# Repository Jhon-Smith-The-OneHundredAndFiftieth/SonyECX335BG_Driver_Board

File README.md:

# This is a driver board for the sony ECX335BG compatible with rasperi py (using the DPI interface)
Basicly a clone of https://github.com/aedancullen/sony-ecx with some things rewired

License : GPL-3.0
gnu.org/licenses/gpl-3.0

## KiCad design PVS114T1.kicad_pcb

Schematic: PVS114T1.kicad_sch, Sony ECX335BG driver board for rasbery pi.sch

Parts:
C1, C17, C22: 4.7uF; C0402
C2, C3, C4, C5, C6, C7, C8, C9, C10, C11, C12, C13, C14, C15, C19, C21: 0.1uF; C0402
C16: 1uF; C0402
C18, C20: 0.01uF; C0402
C23: 0.47uF; C0402
C24: 2.2uF; C0402
C25, C26: 10uF; C0402
J1: 61FVXS-RSM1-GAN-TF_LF__SN_; 61FVXSRSM1GANTFLFSN
J2: Conn_01x08_Male; PinHeader_1x08_P1.00mm_Vertical
JP1: PINHD-2X20; 2X20
L1: ME3220-682MLB; INDPM3228X240N
R1, R2: R0402
R3: 10K; R0402
RN1: YC248-JR-0710KL; YC248JR0710KL
U1: BU90T82-ZE2
U2: LT3473; SON50P300X300X80-9T165X238N
VR1: NCP1117ST33T3G; SOT230P700X170-4

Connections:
/D_6B8B: J2.3, U1.F7 (6B8B)
/D_B10: JP1.7, U1.H5 (B10)
/D_B11: JP1.29, U1.J5 (B11)
/D_B12: JP1.31, U1.H6 (B12)
/D_B13: JP1.26, U1.J6 (B13)
/D_B14: JP1.24, U1.H7 (B14)
/D_B15: JP1.21, U1.J7 (B15)
/D_B16: JP1.19, U1.H8 (B16)
/D_B17: JP1.23, U1.J8 (B17)
/D_CLKIN: JP1.27, U1.F9 (CLKIN)
/D_DDRN: J2.5, U1.E9 (DDRN)
/D_DE: JP1.28, U1.G9 (DE)
/D_FLIP: J2.1, U1.C2 (FLIP)
/D_G10: JP1.32, U1.H1 (G10)
/D_G11: JP1.33, U1.J1 (G11)
/D_G12: JP1.8, U1.H2 (G12)
/D_G13: JP1.10, U1.J2 (G13)
/D_G14: JP1.36, U1.H3 (G14)
/D_G15: JP1.11, U1.J3 (G15)
/D_G16: JP1.12, U1.H4 (G16)
/D_G17: JP1.35, U1.J4 (G17)
/D_HSYNC: JP1.5, U1.J9 (HSYNC)
/D_MAP: J2.2, U1.E8 (MAP)
/D_MODE: J2.4, U1.E7 (MODE)
/D_OE: J2.6, U1.D9 (OE)
/D_PWDN: R3.2, U1.D8 (PWDN)
/D_R10: JP1.38, U1.D2 (R10)
/D_R11: JP1.40, U1.D1 (R11)
/D_R12: JP1.15, U1.E2 (R12)
/D_R13: JP1.16, U1.E1 (R13)
/D_R14: JP1.18, U1.F2 (R14)
/D_R15: JP1.22, U1.F1 (R15)
/D_R16: JP1.37, U1.G2 (R16)
/D_R17: U1.G1 (R17)
/D_RF: J2.8, U1.G8 (RF)
/D_RS: J2.7, U1.F8 (RS)
/D_SI: RN1.4
/D_SI1V8: J1.52, RN1.1, RN1.3
/D_SO1V8: J1.51
/D_TEST: U1.C3 (TEST)
/D_VSYNC: JP1.3, U1.H9 (VSYNC)
/D_XCLR: RN1.12
/D_XCLR1V8: C4.2, J1.47, RN1.9, RN1.11
/D_XCS: RN1.8
/D_XCS1V8: J1.54, RN1.5, RN1.7
/D_XSCK: RN1.16
/D_XSCK1V8: J1.53, RN1.13, RN1.15
/N$1: C1.1, C17.1, J1.2, J1.60
/N$2: L1.1, U2.8 (SW)
/N$4: C23.1, R2.2, U2.1 (CAP)
/N$5: R1.2, R2.1, U2.4 (FB)
/N$8: C11.1, J1.8
/N$9: C12.2, J1.7
/N$10: C13.1, J1.6
/N$11: C14.2, J1.5
/N$12: C15.1, J1.4
/N$13: C16.2, J1.3
/PP1V8_LD1: C3.2, C5.2, C6.2, C7.1, C8.2, C9.2, C20.2, C21.2, C26.1, J1.11, J1.13, J1.26, J1.31, J1.45, J1.48, J1.57, U1.C5 (VDD), U1.C7 (VDD), U1.D3 (VDD), U1.G3 (VDD), U1.G5 (VDD), VR1.2 (OUT)
/PP3V3_VO4: C18.2, C19.2, C22.1, C25.1, JP1.1, JP1.17, L1.2, U1.G7 (VDDIO), U2.3 (CTRL), U2.6 (~SHDN), U2.7 (VIN), VR1.3 (IN)
/PP10V0_BST: C2.2, C10.2, C24.1, J1.9, J1.59, U2.2 (OUT)
/TA1_N: J1.40, U1.B1 (TA1-)
/TA1_P: J1.41, U1.A1 (TA1+)
/TA2_N: J1.22, U1.B6 (TA2-)
/TA2_P: J1.23, U1.A6 (TA2+)
/TB1_N: J1.38, U1.B2 (TB1-)
/TB1_P: J1.39, U1.A2 (TB1+)
/TB2_N: J1.20, U1.B7 (TB2-)
/TB2_P: J1.21, U1.A7 (TB2+)
/TC1_N: J1.36, U1.B3 (TC1-)
/TC1_P: J1.37, U1.A3 (TC1+)
/TC2_N: J1.18, U1.B8 (TC2-)
/TC2_P: J1.19, U1.A8 (TC2+)
/TCLK1_N: J1.42, U1.B4 (TCLK1-)
/TCLK1_P: J1.43, U1.A4 (TCLK1+)
/TCLK2_N: J1.14, U1.B9 (TCLK2-)
/TCLK2_P: J1.15, U1.A9 (TCLK2+)
/TD1_N: J1.34, U1.B5 (TD1-)
/TD1_P: J1.35, U1.A5 (TD1+)
/TD2_N: J1.16, U1.C8 (TD2-)
/TD2_P: J1.17, U1.C9 (TD2+)
GND: C1.2, C2.1, C3.1, C4.1, C5.1, C6.1, C7.2, C8.1, C9.1, C10.1, C11.2, C12.1, C13.2, C14.1, C15.2, C16.1, C17.2, C18.1, C19.1, C20.1, C21.1, C22.2, C23.2, C24.2, C25.2, C26.2, J1.1, J1.10, J1.12, J1.24, J1.25, J1.27, J1.28, J1.29, J1.30, J1.32, J1.33, J1.46, J1.49, J1.55, J1.56, J1.58, J1.61, J1.MP1, J1.MP2, JP1.6, JP1.9, JP1.14, JP1.20, JP1.25, JP1.30, JP1.34, JP1.39, R1.1, R3.1, RN1.2, RN1.6, RN1.10, RN1.14, U1.C4 (GND), U1.C6 (GND), U1.D7 (GND), U1.E3 (GND), U1.F3 (GND), U1.G4 (GND), U1.G6 (GND), U2.9 (GND), VR1.1 (GND)

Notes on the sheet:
SONY ECX337A
LV1A
LV6A
TEST
VCATH
VCAL
VDD1IF
LVCLK0A
VDD1
VSSIF
8x 10K
VG255
VCCP_I
VG0
LV0B
VOFS
LVCLK0B
LV9A
LV3B
LV3A
LV8A
LVCLK1A
LV4B
VGC
LV6B
LV5B
LV1B
LV4A
LV7B
VSS
LV8B
VDD2
LV5A
LV0A
XSCK
LV2A
VCCP_O
XCS
LV7A
LVCLK1B

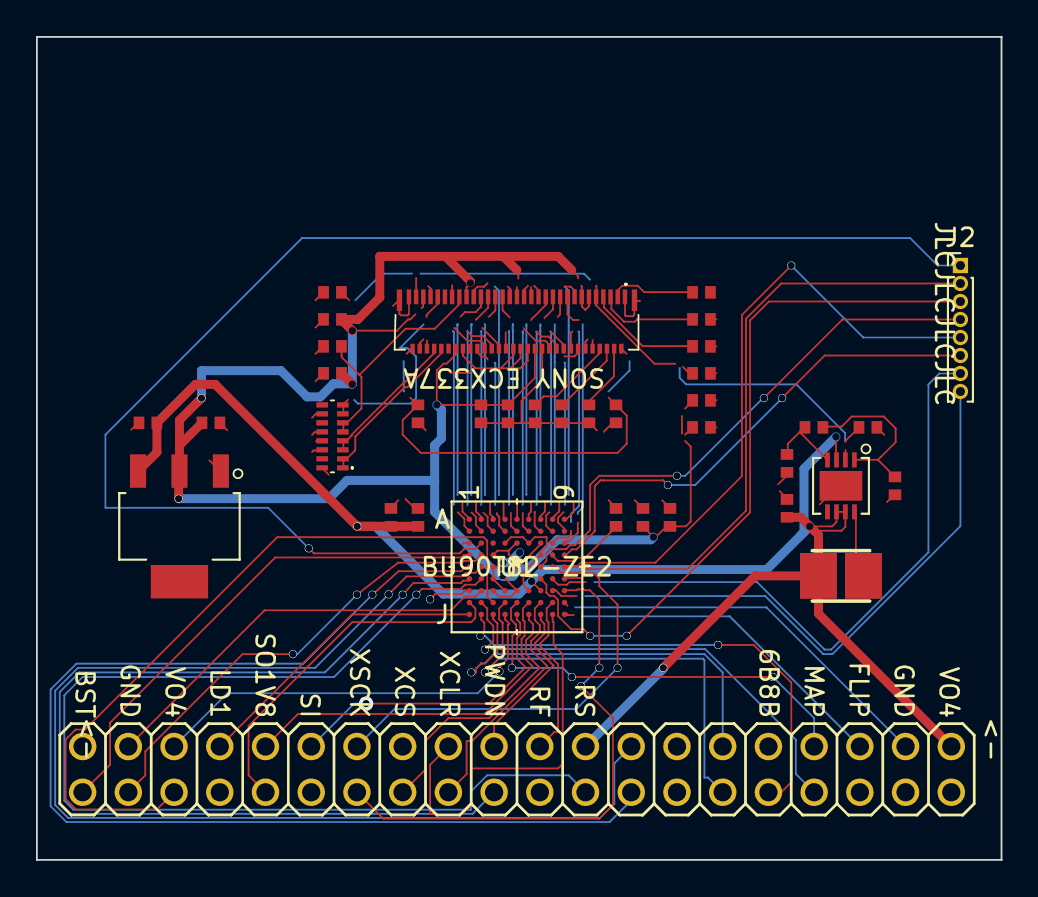
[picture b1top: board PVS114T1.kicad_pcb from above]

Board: 4 copper layers, 53.6 x 45.7 mm, 37 parts (0 on the bottom side), 74 nets.

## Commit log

2023-01-09 Adding files new file: #auto_saved_files# new file: PVS114T1-backups/PVS114T1-2023-01-01_153635.zip new file: PVS114T1-backups/PVS114T1-2023-01-07_203742.zip new file: PVS114T1-backups/PVS114T1-2023-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
2023-01-09 Added Readme modified: README.md
2023-01-09 Added license to shematic
2023-01-09 Added a pin header for the config pins modified: PVS114T1.kicad_pcb modified: PVS114T1.kicad_prl modified: PVS114T1.kicad_sch
2023-01-09 Added headear for config pins in pcb and routed wires modified: PVS114T1.kicad_pcb
2023-01-10 Conected unconected trace

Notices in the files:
PVS114T1.kicad_pcb:
Lisence : GPL-3.0
parts and their libraries:
Copyright 2021 Accelerated Designs. All rights reserved.
